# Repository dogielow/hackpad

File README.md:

i dont have the ssd1306 and cherry mx 3d model!
# hackpad
my contribution to hackclubs blueprint!
I found this project litellary on instagram at the end of its deadline, i have in a next project already started for blueprint.
In this project i will fix the code as i can already feel it wont work as i intended.
ssd1306 oled display fits above xiao but it doesnt cover it, the xiao board is fully visible.
BOM:
*pla or abs shell (3d files in cad folder)
*4x cherry mx keys 
*pcb (files in pcb folder)
*seeed XIAO rp2040-DIP
*4x sk6812 LED
*adafruit ssd1306 oled
* two female-female arduino cables
*a lot of love
schematic 

pcb

with xiao

case assembled

top cover

bottom shell

pcb in 3d

ssd1306

the two cables need to be cut in half, stripped and soldered to GPIO6 as sda and GPIO7 as scl, gnd and 5v. the ssd1036 has to be glued in to the hole in the top left.

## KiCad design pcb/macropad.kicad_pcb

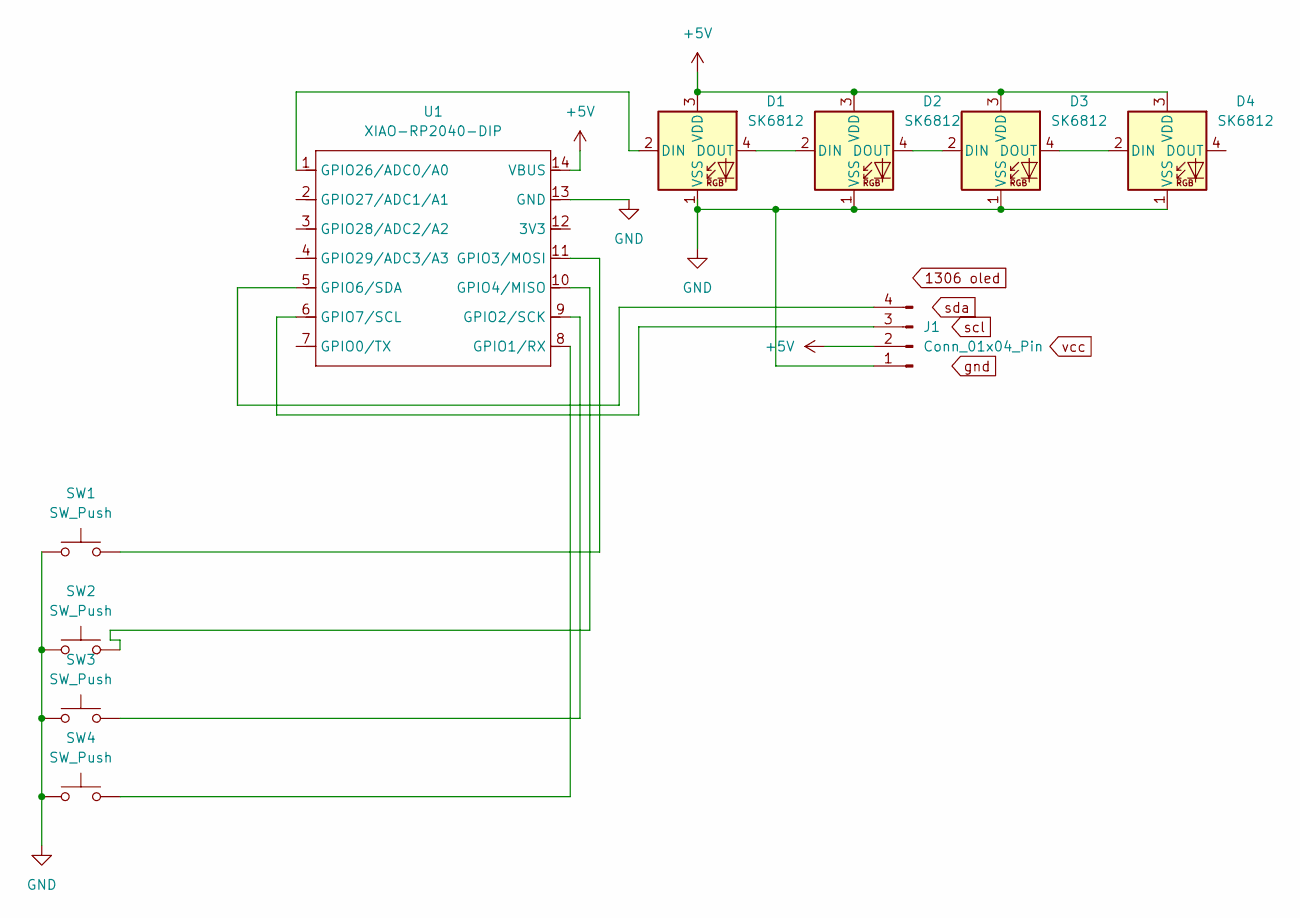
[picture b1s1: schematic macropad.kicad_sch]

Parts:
D1, D2, D3, D4: SK6812; LED_SK6812_PLCC4_5.0x5.0mm_P3.2mm
J1: Conn_01x04_Pin
SW1, SW2, SW3, SW4: SW_Push; SW_Cherry_MX_1.00u_PCB
U1: XIAO-RP2040-DIP

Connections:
+5V: D1.3 (VDD), D2.3 (VDD), D3.3 (VDD), D4.3 (VDD), J1.2, U1.14 (VBUS)
GND: D1.1 (VSS), D2.1 (VSS), D3.1 (VSS), D4.1 (VSS), J1.1, SW1.1, SW2.1, SW3.1, SW4.1, U1.13 (GND)
unnamed: D1.2 (DIN), U1.1 (GPIO26/ADC0/A0)
unnamed: D1.4 (DOUT), D2.2 (DIN)
unnamed: D2.4 (DOUT), D3.2 (DIN)
unnamed: D3.4 (DOUT), D4.2 (DIN)
unnamed: J1.3, U1.6 (GPIO7/SCL)
unnamed: J1.4, U1.5 (GPIO6/SDA)
unnamed: SW4.2, U1.8 (GPIO1/RX)
unnamed: SW3.2, U1.9 (GPIO2/SCK)
unnamed: SW1.2, U1.11 (GPIO3/MOSI)
unnamed: SW2.2, U1.10 (GPIO4/MISO)

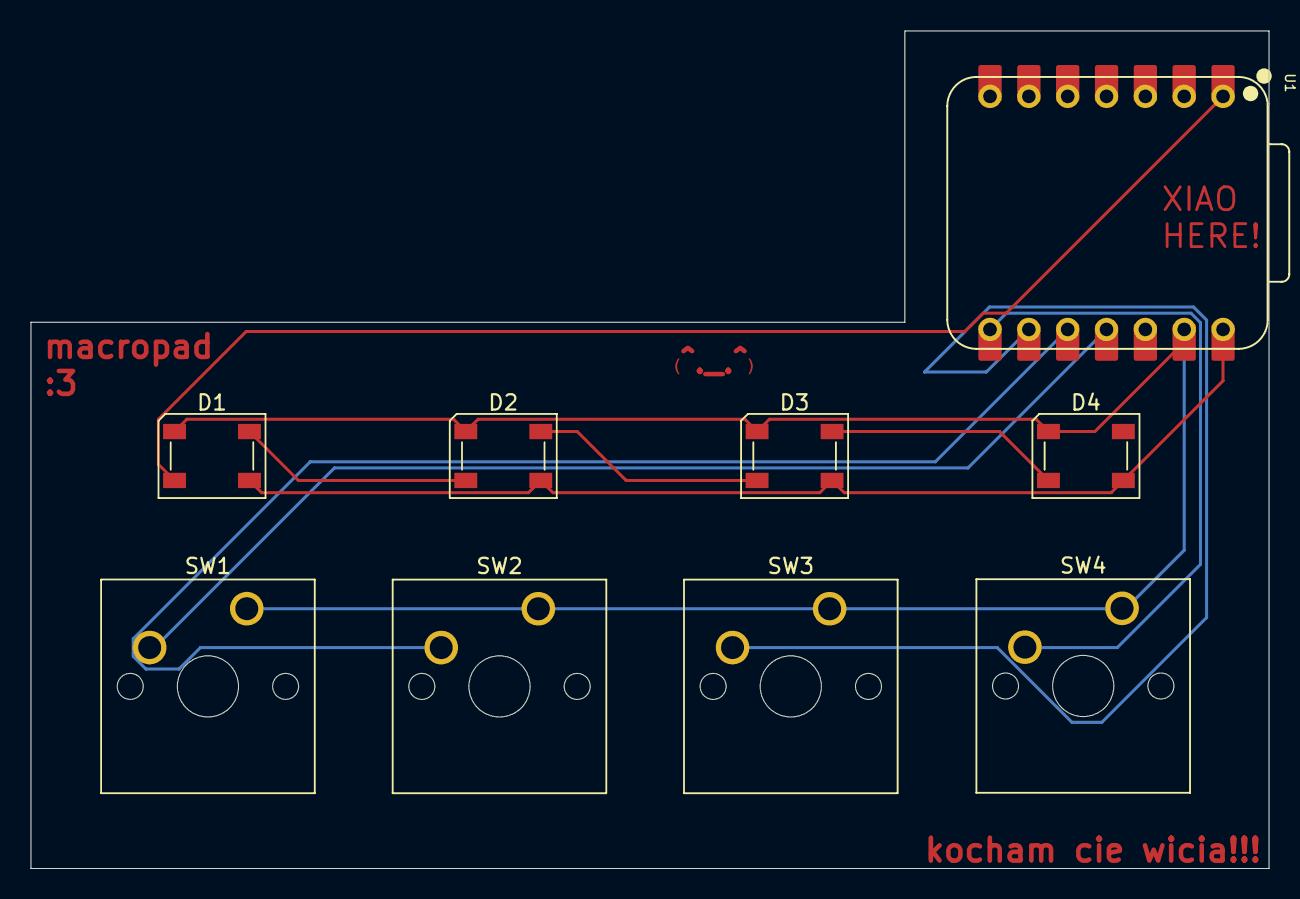
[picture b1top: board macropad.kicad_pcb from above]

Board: 2 copper layers, 81.0 x 54.8 mm, 9 parts (0 on the bottom side), 10 nets.

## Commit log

2026-01-09 Create d
2026-01-09 dodany plik
2026-01-09 Create a
2026-01-09 Create s
